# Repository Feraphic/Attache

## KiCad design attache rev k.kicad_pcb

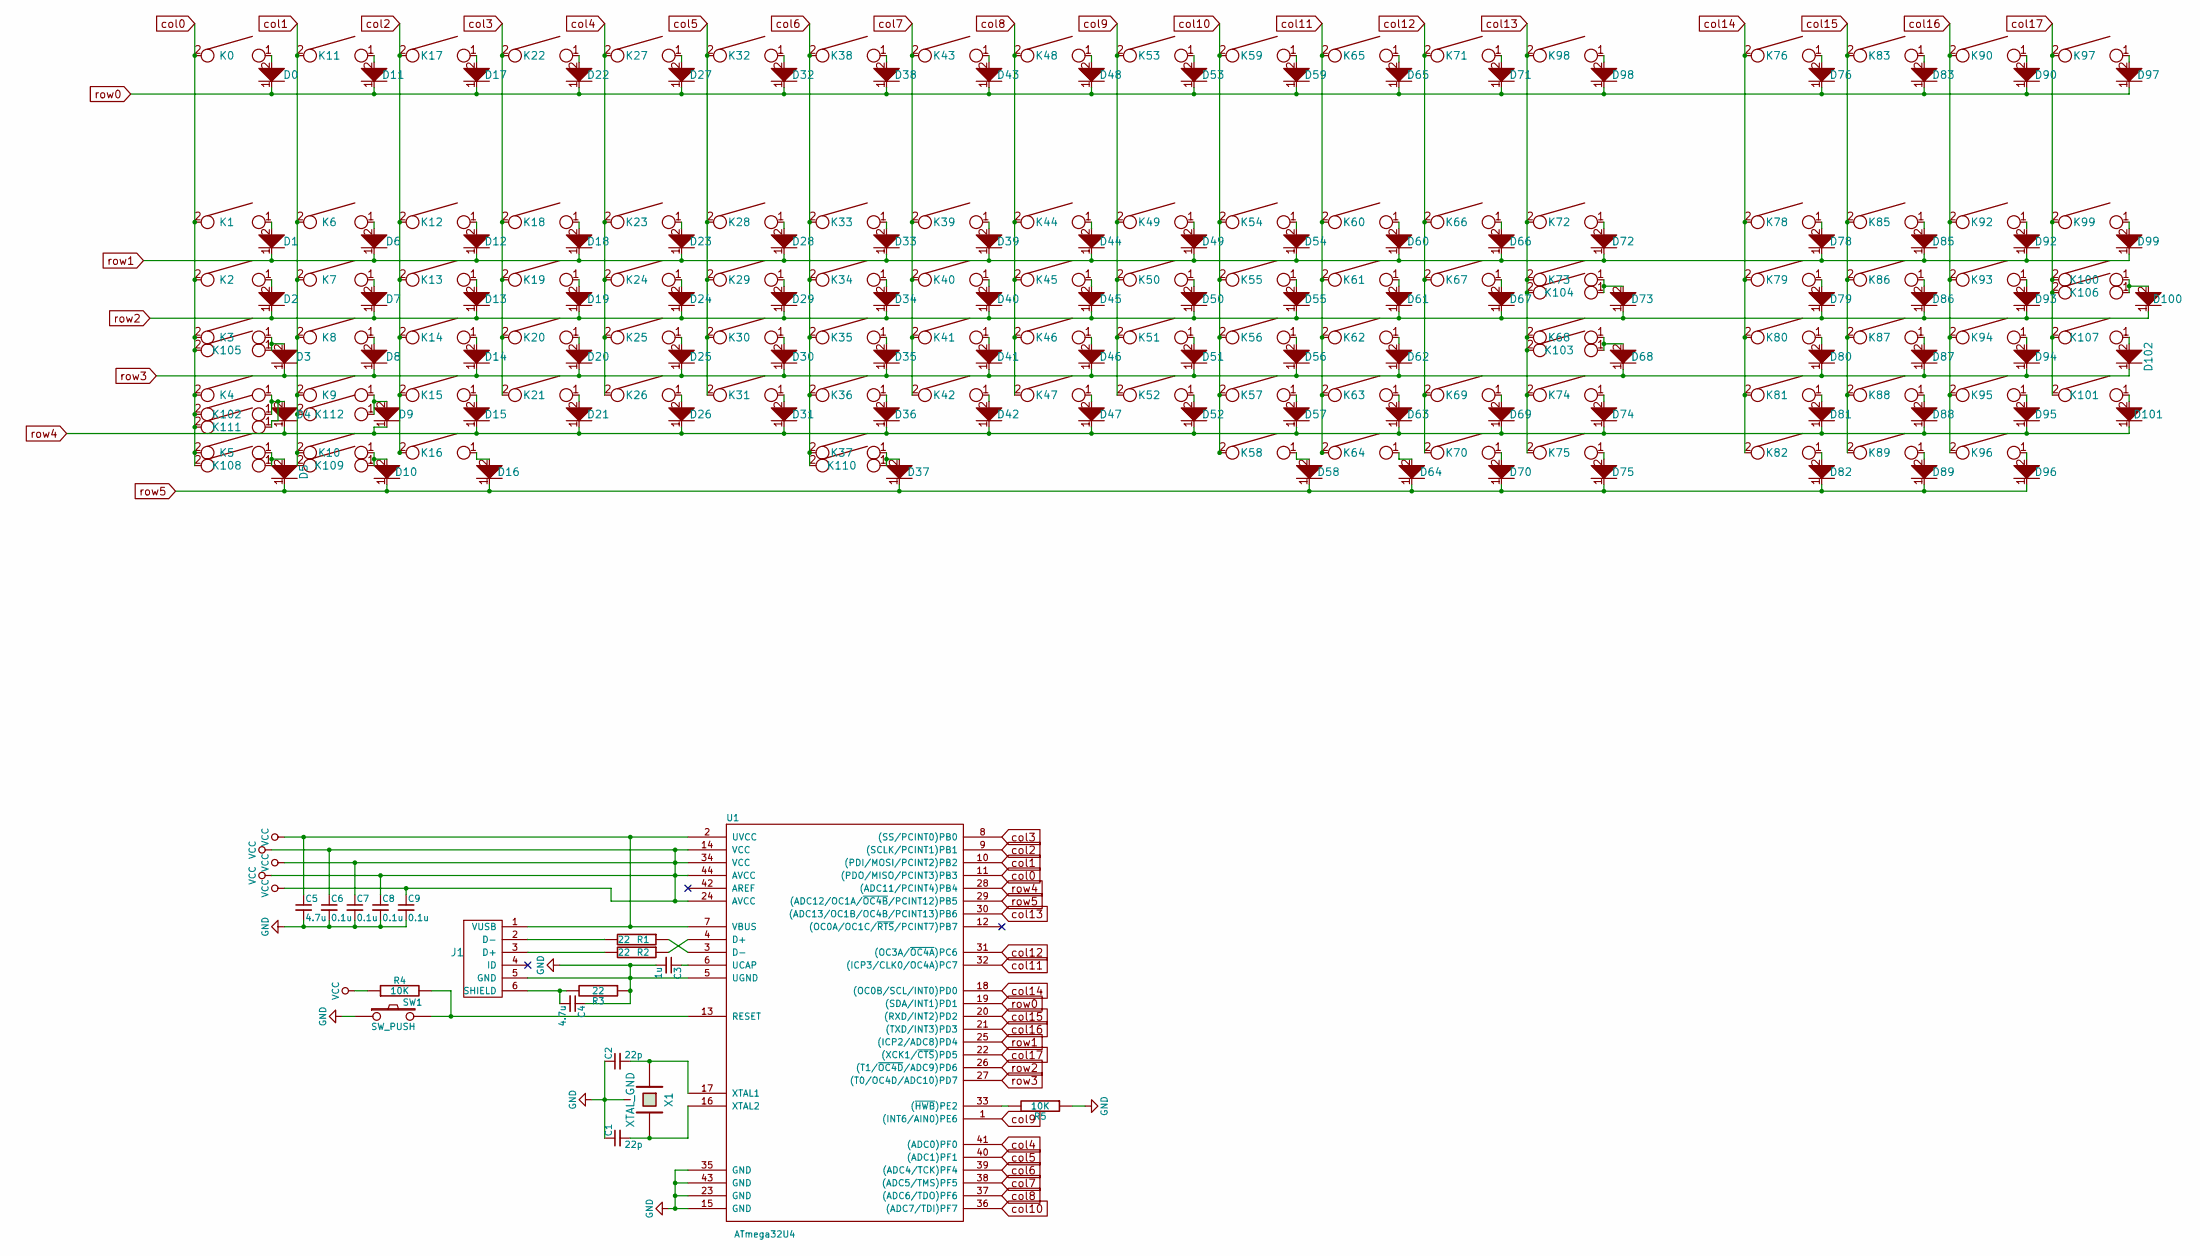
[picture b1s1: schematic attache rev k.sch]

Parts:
C1, C2: 22p; C_0805_HandSoldering
C3: 1u; C_0805_HandSoldering
C4, C5: 4.7u; C_0805_HandSoldering
C6, C7, C8, C9: 0.1u; C_0805_HandSoldering
D0, D1, D2, D3, D4, D5, D6, D7, D8, D9, D10, D11, D12, D13, D14, D15, D16, D17, D18, D19, D20, D21, D22, D23, D24, D25, D26, D27, D28, D29, D30, D31, D32, D33, D34, D35, D36, D37, D38, D39, D40, D41, D42, D43, D44, D45, D46, D47, D48, D49, D50, D51, D52, D53, D54, D55, D56, D57, D58, D59, D60, D61, D62, D63, D64, D65, D66, D67, D68, D69, D70, D71, D72, D73, D74, D75, D76, D78, D79, D80, D81, D82, D83, D85, D86, D87, D88, D89, D90, D92, D93, D94, D95, D96, D97, D98, D99, D100, D101, D102: D; D_SOD123_axial
J1: USB_mini_micro_B; USB_miniB_hirose_5S8
K0, K1, K2, K3, K4, K5, K6, K7, K8, K9, K10, K11, K12, K13, K14, K15, K16, K17, K18, K19, K20, K21, K22, K23, K24, K25, K26, K27, K28, K29, K30, K31, K32, K33, K34, K35, K36, K37, K38, K39, K40, K41, K42, K43, K44, K45, K46, K47, K48, K49, K50, K51, K52, K53, K54, K55, K56, K57, K58, K59, K60, K61, K62, K63, K64, K65, K66, K67, K68, K69, K70, K71, K72, K73, K74, K75, K76, K78, K79, K80, K81, K82, K83, K85, K86, K87, K88, K89, K90, K92, K93, K94, K95, K96, K97, K98, K99, K100, K101, K102, K103, K104, K105, K106, K107, K108, K109, K110, K111, K112: KEYSW; SW_PCB_2PIN
R1, R2, R3: 22; R_0805_HandSoldering
R4, R5: 10K; R_0805_HandSoldering
SW1: SW_PUSH; SW_SPST_TL3342
U1: ATmega32U4; TQFP-44_10x10mm_Pitch0.8mm
X1: XTAL_GND; crystal_FA238-TSX3225

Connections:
GND: C1.1, C2.1, C3.2, C4.1, C5.2, C6.2, C7.2, C8.2, C9.2, J1.5 (GND), R3.1, R5.1, SW1.1, U1.5 (UGND), U1.15 (GND), U1.23 (GND), U1.35 (GND), U1.43 (GND), X1.3
unnamed: C1.2, U1.16 (XTAL2), X1.2
unnamed: C2.2, U1.17 (XTAL1), X1.1
unnamed: C3.1, U1.6 (UCAP)
unnamed: C4.2, J1.6 (SHIELD), R3.2
unnamed: D0.2, K0.1
unnamed: D1.2, K1.1
unnamed: D2.2, K2.1
unnamed: D3.2, K3.1, K105.1
unnamed: D4.2, K4.1, K102.1, K111.1
unnamed: D5.2, K5.1, K108.1
unnamed: D6.2, K6.1
unnamed: D7.2, K7.1
unnamed: D8.2, K8.1
unnamed: D9.2, K9.1, K112.1
unnamed: D10.2, K10.1, K109.1
unnamed: D11.2, K11.1
unnamed: D12.2, K12.1
unnamed: D13.2, K13.1
unnamed: D14.2, K14.1
unnamed: D15.2, K15.1
unnamed: D16.2, K16.1
unnamed: D17.2, K17.1
unnamed: D18.2, K18.1
unnamed: D19.2, K19.1
unnamed: D20.2, K20.1
unnamed: D21.2, K21.1
unnamed: D22.2, K22.1
unnamed: D23.2, K23.1
unnamed: D24.2, K24.1
unnamed: D25.2, K25.1
unnamed: D26.2, K26.1
unnamed: D27.2, K27.1
unnamed: D28.2, K28.1
unnamed: D29.2, K29.1
unnamed: D30.2, K30.1
unnamed: D31.2, K31.1
unnamed: D32.2, K32.1
unnamed: D33.2, K33.1
unnamed: D34.2, K34.1
unnamed: D35.2, K35.1
unnamed: D36.2, K36.1
unnamed: D37.2, K37.1, K110.1
unnamed: D38.2, K38.1
unnamed: D39.2, K39.1
unnamed: D40.2, K40.1
unnamed: D41.2, K41.1
unnamed: D42.2, K42.1
unnamed: D43.2, K43.1
unnamed: D44.2, K44.1
unnamed: D45.2, K45.1
unnamed: D46.2, K46.1
unnamed: D47.2, K47.1
unnamed: D48.2, K48.1
unnamed: D49.2, K49.1
unnamed: D50.2, K50.1
unnamed: D51.2, K51.1
unnamed: D52.2, K52.1
unnamed: D53.2, K53.1
unnamed: D54.2, K54.1
unnamed: D55.2, K55.1
unnamed: D56.2, K56.1
unnamed: D57.2, K57.1
unnamed: D58.2, K58.1
unnamed: D59.2, K59.1
unnamed: D60.2, K60.1
unnamed: D61.2, K61.1
unnamed: D62.2, K62.1
unnamed: D63.2, K63.1
unnamed: D64.2, K64.1
unnamed: D65.2, K65.1
unnamed: D66.2, K66.1
unnamed: D67.2, K67.1
unnamed: D68.2, K68.1, K103.1
unnamed: D69.2, K69.1
unnamed: D70.2, K70.1
unnamed: D71.2, K71.1
unnamed: D72.2, K72.1
unnamed: D73.2, K73.1, K104.1
unnamed: D74.2, K74.1
unnamed: D75.2, K75.1
unnamed: D76.2, K76.1
unnamed: D78.2, K78.1
unnamed: D79.2, K79.1
unnamed: D80.2, K80.1
unnamed: D81.2, K81.1
unnamed: D82.2, K82.1
unnamed: D83.2, K83.1
unnamed: D85.2, K85.1
unnamed: D86.2, K86.1
unnamed: D87.2, K87.1
unnamed: D88.2, K88.1
unnamed: D89.2, K89.1
unnamed: D90.2, K90.1
unnamed: D92.2, K92.1
unnamed: D93.2, K93.1
unnamed: D94.2, K94.1
unnamed: D95.2, K95.1
unnamed: D96.2, K96.1
unnamed: D97.2, K97.1
unnamed: D98.2, K98.1
unnamed: D99.2, K99.1
unnamed: D100.2, K100.1, K106.1
unnamed: D101.2, K101.1
unnamed: D102.2, K107.1
unnamed: J1.2 (D-), R1.2
unnamed: J1.3 (D+), R2.2
unnamed: R1.1, U1.3 (D-)
unnamed: R2.1, U1.4 (D+)
unnamed: R4.2, SW1.2, U1.13 (RESET)
unnamed: R5.2, U1.33 ((~HWB~)PE2)
VCC: C5.1, C6.1, C7.1, C8.1, C9.1, J1.1 (VUSB), R4.1, U1.2 (UVCC), U1.7 (VBUS), U1.14 (VCC), U1.24 (AVCC), U1.34 (VCC), U1.44 (AVCC)
col0: K0.2, K1.2, K2.2, K3.2, K4.2, K5.2, K102.2, K105.2, K108.2, K111.2, U1.11 ((PDO/MISO/PCINT3)PB3)
col1: K6.2, K7.2, K8.2, K9.2, K10.2, K11.2, K109.2, K112.2, U1.10 ((PDI/MOSI/PCINT2)PB2)
col2: K12.2, K13.2, K14.2, K15.2, K16.2, K17.2, U1.9 ((SCLK/PCINT1)PB1)
col3: K18.2, K19.2, K20.2, K21.2, K22.2, U1.8 ((SS/PCINT0)PB0)
col4: K23.2, K24.2, K25.2, K26.2, K27.2, U1.41 ((ADC0)PF0)
col5: K28.2, K29.2, K30.2, K31.2, K32.2, U1.40 ((ADC1)PF1)
col6: K33.2, K34.2, K35.2, K36.2, K37.2, K38.2, K110.2, U1.39 ((ADC4/TCK)PF4)
col7: K39.2, K40.2, K41.2, K42.2, K43.2, U1.38 ((ADC5/TMS)PF5)
col8: K44.2, K45.2, K46.2, K47.2, K48.2, U1.37 ((ADC6/TDO)PF6)
col9: K49.2, K50.2, K51.2, K52.2, K53.2, U1.1 ((INT6/AIN0)PE6)
col10: K54.2, K55.2, K56.2, K57.2, K58.2, K59.2, U1.36 ((ADC7/TDI)PF7)
col11: K60.2, K61.2, K62.2, K63.2, K64.2, K65.2, U1.32 ((ICP3/CLK0/OC4A)PC7)
col12: K66.2, K67.2, K69.2, K70.2, K71.2, U1.31 ((OC3A/~OC4A~)PC6)
col13: K68.2, K72.2, K73.2, K74.2, K75.2, K98.2, K103.2, K104.2, U1.30 ((ADC13/OC1B/OC4B/PCINT13)PB6)
col14: K76.2, K78.2, K79.2, K80.2, K81.2, K82.2, U1.18 ((OC0B/SCL/INT0)PD0)
col15: K83.2, K85.2, K86.2, K87.2, K88.2, K89.2, U1.20 ((RXD/INT2)PD2)
col16: K90.2, K92.2, K93.2, K94.2, K95.2, K96.2, U1.21 ((TXD/INT3)PD3)
col17: K97.2, K99.2, K100.2, K101.2, K106.2, K107.2, U1.22 ((XCK1/~CTS~)PD5)
row0: D0.1, D11.1, D17.1, D22.1, D27.1, D32.1, D38.1, D43.1, D48.1, D53.1, D59.1, D65.1, D71.1, D76.1, D83.1, D90.1, D97.1, D98.1, U1.19 ((SDA/INT1)PD1)
row1: D1.1, D6.1, D12.1, D18.1, D23.1, D28.1, D33.1, D39.1, D44.1, D49.1, D54.1, D60.1, D66.1, D72.1, D78.1, D85.1, D92.1, D99.1, U1.25 ((ICP2/ADC8)PD4)
row2: D2.1, D7.1, D13.1, D19.1, D24.1, D29.1, D34.1, D40.1, D45.1, D50.1, D55.1, D61.1, D67.1, D73.1, D79.1, D86.1, D93.1, D100.1, U1.26 ((T1/~OC4D~/ADC9)PD6)
row3: D3.1, D8.1, D14.1, D20.1, D25.1, D30.1, D35.1, D41.1, D46.1, D51.1, D56.1, D62.1, D68.1, D80.1, D87.1, D94.1, D102.1, U1.27 ((T0/OC4D/ADC10)PD7)
row4: D4.1, D9.1, D15.1, D21.1, D26.1, D31.1, D36.1, D42.1, D47.1, D52.1, D57.1, D63.1, D69.1, D74.1, D81.1, D88.1, D95.1, D101.1, U1.28 ((ADC11/PCINT4)PB4)
row5: D5.1, D10.1, D16.1, D37.1, D58.1, D64.1, D70.1, D75.1, D82.1, D89.1, D96.1, U1.29 ((ADC12/OC1A/~OC4B~/PCINT12)PB5)

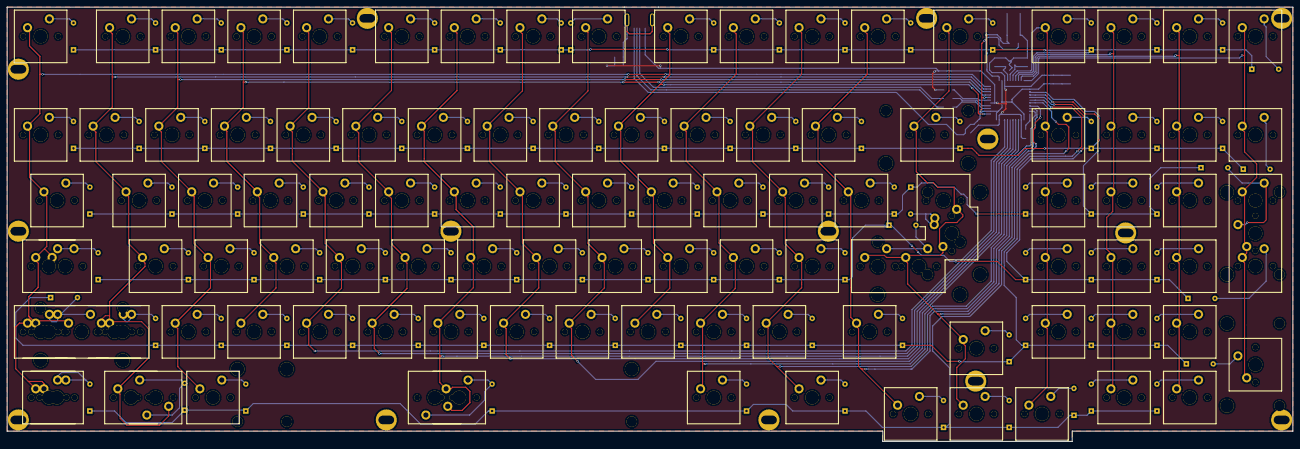
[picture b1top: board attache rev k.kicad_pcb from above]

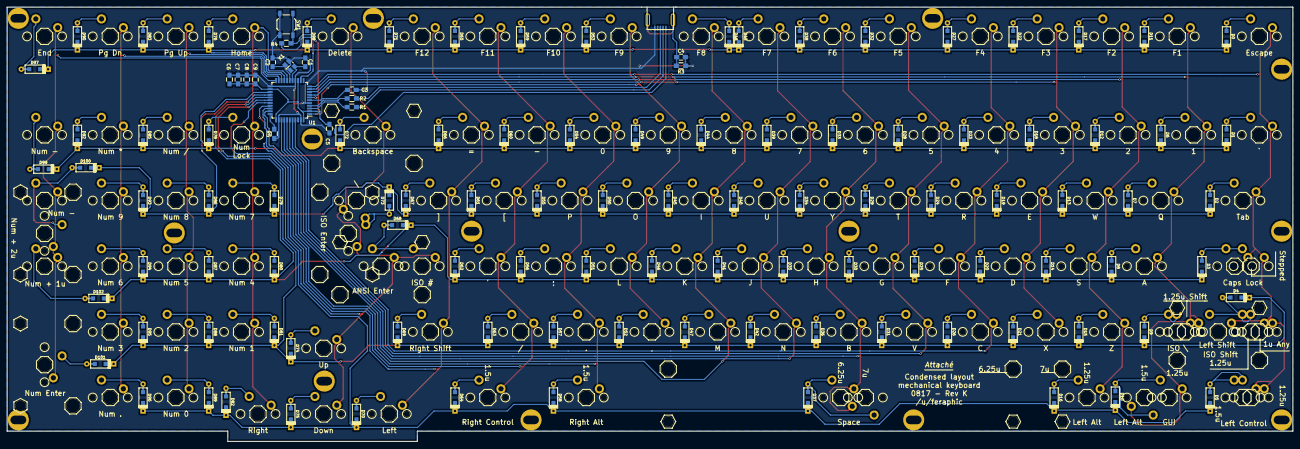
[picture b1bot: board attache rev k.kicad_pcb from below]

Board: 2 copper layers, 373.0 x 126.0 mm, 250 parts (118 on the bottom side), 136 nets.

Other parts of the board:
6.25_?, 6.25_?#2: VAL**; STAB_A3940
A940_?, A940_?#2, A940_?#3, A940_?#4, A940_?#5, A940_?#6: VAL**; STAB_A940
Poker_oval_hole: VAL**; Poker_oval_hole
Poker_oval_hole#2, Poker_oval_hole#3, Poker_oval_hole#4, Poker_oval_hole#5, Poker_oval_hole#6, Poker_oval_hole#7, Poker_oval_hole#8, Poker_oval_hole#9, Poker_oval_hole#10, Poker_oval_hole#11, Poker_oval_hole#12, Poker_oval_hole#13, Poker_oval_hole#14: VAL**; Poker_oval_hole

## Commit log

2017-08-15 Attache Keyboard
2017-08-15 Attache
